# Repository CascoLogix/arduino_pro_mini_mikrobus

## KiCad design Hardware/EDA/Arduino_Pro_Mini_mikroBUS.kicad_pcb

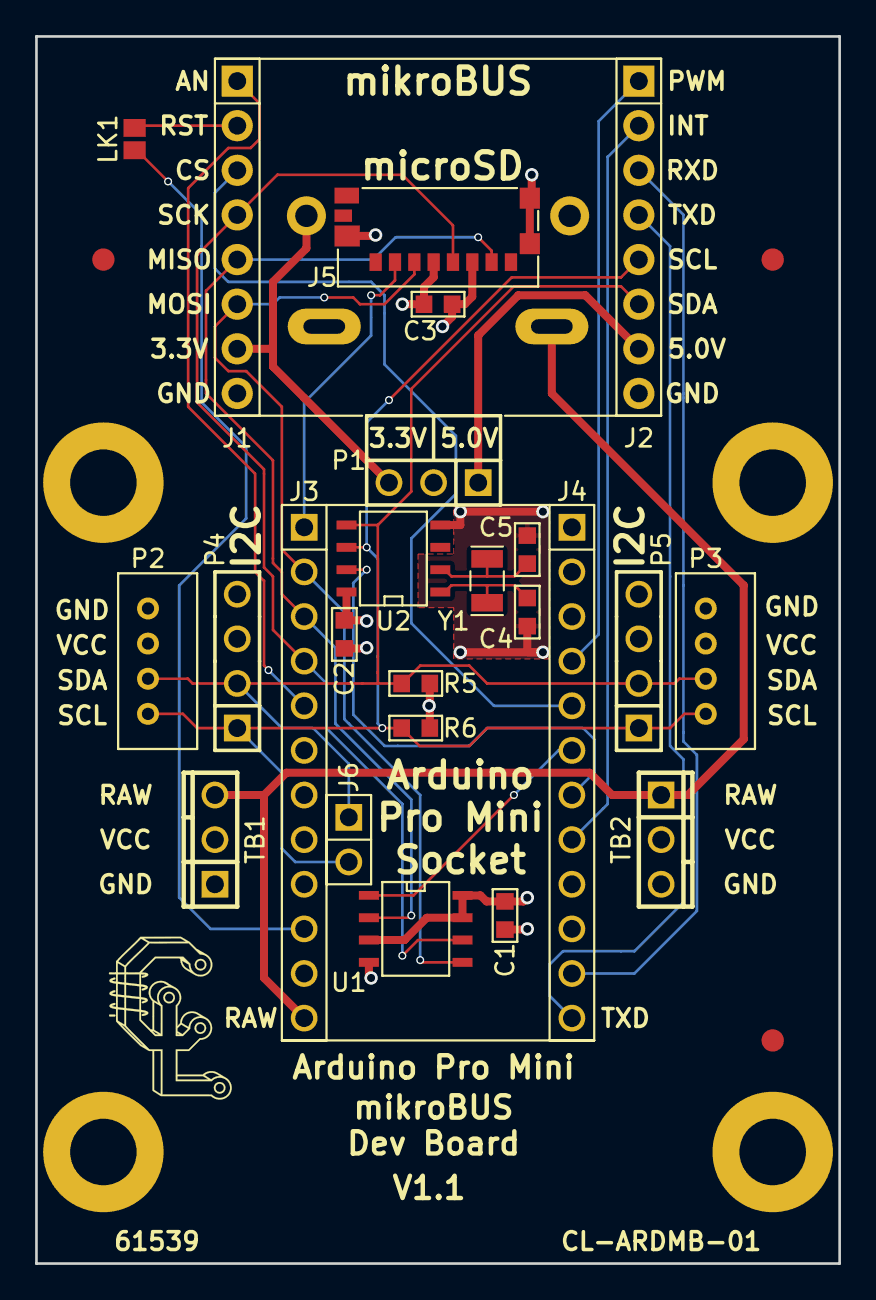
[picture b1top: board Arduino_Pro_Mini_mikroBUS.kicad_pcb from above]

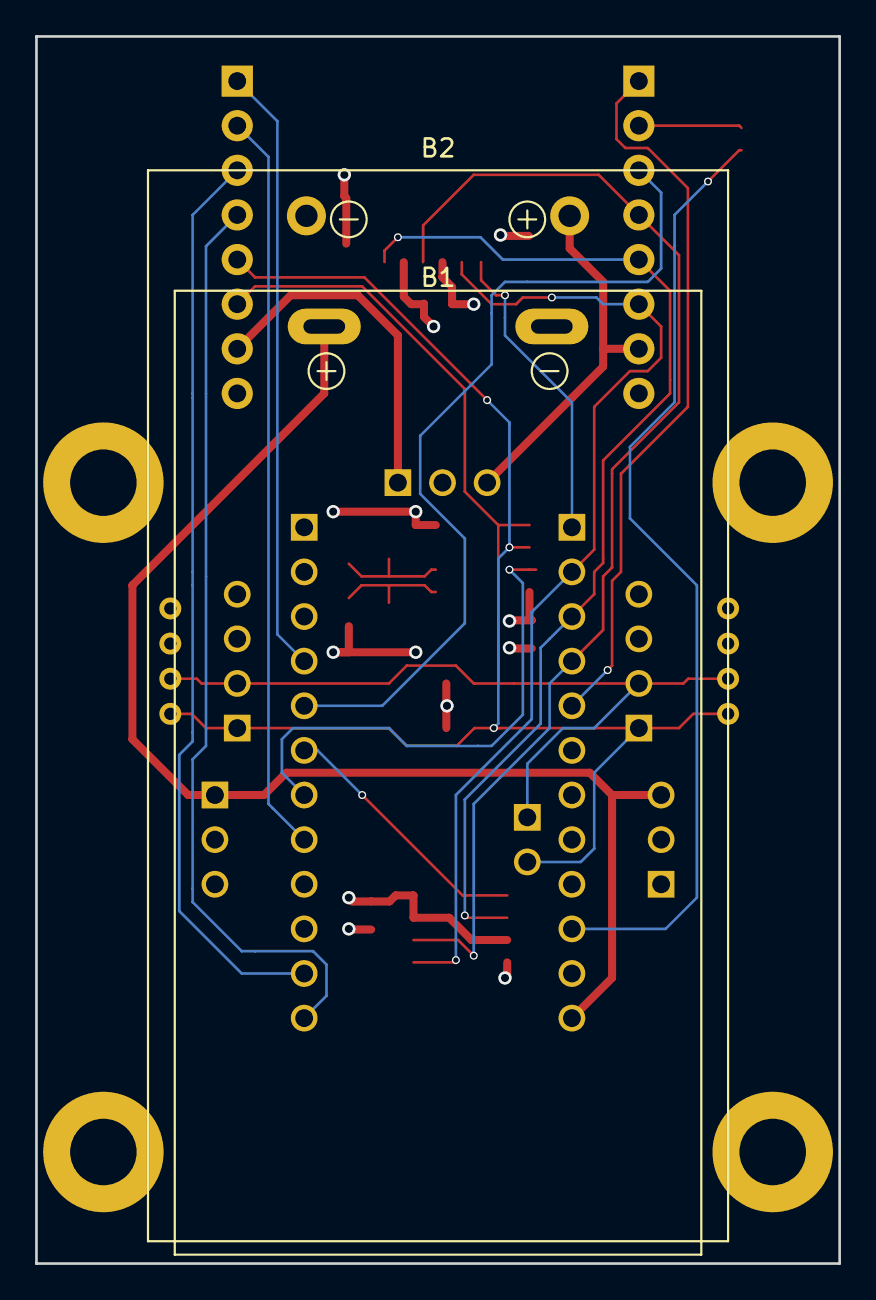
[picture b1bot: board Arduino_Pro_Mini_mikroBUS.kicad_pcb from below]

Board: 4 copper layers, 45.7 x 69.8 mm, 34 parts (2 on the bottom side), 23 nets.

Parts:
B1: 9V; BC9VPC
B2: 2xAA; Keystone_2462_2AA
C1, C2, C3: 1uF; 0603
C4, C5: 6pF; 0603
G1: Casco_Logix_Logo; Casco_Logix_Logo_7x7MM
J1, J2: HEADER_F_2.54MM_1R8P_ST_AU_PTH
J3, J4: HEADER_F_2.54MM_1R12P_ST_AU_PTH; HEADER_F_2.54MM_1R12P_ST_SN_PTH
J5: Molex_0475710001
J6: HEADER_F_2.54MM_1R2P_ST_AU_PTH; HEADER_F_2.54MM_1R2P_ST_SN_PTH
LK1: SOLDER_LINK_NO
M1, M2, M3: FID; FIDUCIAL
MH1, MH2, MH3, MH4: MTG_HOLE; MH_#6
P1: HEADER_M_2.54MM_1R3P_ST_AU_PTH
P2, P3: HEADER_M_2.54MM_1R4P_ST_AU_PTH; PH_2.0_PTH
P4, P5: HEADER_M_2.54MM_1R4P_ST_AU_PTH
R5, R6: 4.7k; R0603
TB1, TB2: OSTVN_1x3; TB_100MIL_1R3P_PTH
U1: FL116K; SO-8
U2: MCP7940M-I/SN; SO-8
Y1: 32.768k; XTAL_3.2MM_1.5MM_SMT_ALT

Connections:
3.3V: B2.1, J1.7, P1.3
5.0V: J2.7, P1.1
/mikroBUS_RST: J1.2, LK1.2
A0: J1.1, J3.5
D2: J2.2, J4.8
D3: J4.7, U2.7
D4: J4.6, U1.1
D5: J1.3, J4.5
D6: J2.1, J4.4
D10: J3.1, J5.2
GND: B1.2, B2.2, C1.2, C2.2, C3.2, C4.2, C5.2, J1.8, J2.8, J3.11, J4.9, J5.6, J5.9, J5.10, J5.11, MH1.~, MH2.~, MH3.~, MH4.~, P2.4, P3.4, P4.4, P5.4, TB1.1, TB2.3, U1.4, U2.4
MISO: J1.5, J3.3, J5.7, U1.2
MOSI: J1.6, J3.2, J5.3, U1.5
unnamed: C4.1, U2.1, Y1.2
unnamed: C5.1, U2.2, Y1.1
RAW: B1.1, J3.12, TB1.3, TB2.1
RST: J3.10, LK1.1
RXD: J2.3, J4.11
SCK: J1.4, J3.4, J5.5, U1.6
SCL: J2.5, J6.2, P2.1, P3.1, P4.1, P5.1, R6.2, U2.6
SDA: J2.6, J6.1, P2.2, P3.2, P4.2, P5.2, R5.2, U2.5
TXD: J2.4, J4.12
VCC: C1.1, C2.1, C3.1, J3.9, J5.4, P1.2, P2.3, P3.3, P4.3, P5.3, R5.1, R6.1, TB1.2, TB2.2, U1.3, U1.7, U1.8, U2.8

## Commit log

2017-12-27 Initial commit.
2017-12-27 Changed uSD CS pin to D10. Connected mikroBUS PWM pin to D6. Altered front silkscreen. Generated PDF schematic and Gerbers.
2017-12-28 Updated silkscreen artwork. Generated new gerbers and BOM.
2017-12-28 Corrected part# on silkscreen artwork.
2017-12-29 Added PCB render image.
2017-12-29 Updated bad 3D model links.
2018-01-03 Removed barrel jack connector due to interference with Arduino Pro Mini. Updated schematic, layout and generated new gerbers. Added BOM file.
2018-01-05 Move location of P1 down slightly to allow more room for mikroBUS module PCB.
2018-01-05 Updated PCB render images.
2018-01-06 Changed PCB outline/size to accomodate mounting holes, but still fit in enclosure. Regenerated Gerbers and PCB render images.
2018-01-14 Found error in BOM as exported from schematic. Grove connectors had wrong footprint assigned. Corrected mistake in schematic and updated netlist and BOM.
2018-02-12 Initial updates based on first build and testing. Final updates to be pushed in subsequent commit(s).
2018-02-17 Few more updates.
2018-04-07 Added layout for RTC crystal and caps. Re-routed several traces as-needed. Updated RTC and crystal component parameters in schematic and regenerated netlist. Gerbers generated - need final review bef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
2018-04-07 Updated date in schematic and PCB title block. Regenerated PDF schematic. Verified gerbers.
2018-05-06 Updated BOM to include 32.768 Xtal.
